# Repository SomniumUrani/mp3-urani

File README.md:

# MP3 - Urani House

## Button layout

## Electric chars

| Description   | Num             | V min | typ | V max | mA  |
| ------------- | --------------- | ----- | --- | ----- | --- |
| MCU           | STM32F412       | 1.7   | -   | 3.6   | 30  |
| MCU           | ESP32           | 3     | 3.3 | 3.6   | 450 |
| LCD backlight | HS24CG003-ARX   | 2.8   | 3   | 3.2   | 80  |
| LCD vdd       | NHS24CG003-ARXA | 1.65  | 1.8 | 3.3   | -   |
| IO expander   | PCF8574T        | 2.5   | -   | 6     | 25  |
| DAC           | PCM5102A        | 3.1   | 3.3 | 3.46  | 10  |

## Components stuff
### Special outsource components on PCB

| Name                  | MPN                   | Source | Source No. | Description                                                                                 |
| --------------------- | --------------------- | ------ | ---------- | ------------------------------------------------------------------------------------------- |
| LCD                   | HS24CG003-ARX         | LCSC   | C5329583   | 240*320 dots (RGB) SPI INTERFACE                                                            |
| FPC connector for LCD | LW10251-16            | LCSC   | C375934    | CONN FFC FPC 16POS 1mm TOP CNT SMD R/A                                                      |
| TF slot               | TF PUSH               | LCSC   | C393941    | CONN MICRO SD CARD (TF CARD) PUSH-PUSH SMD                                                  |
| Debug Slider          | YSSP2AG00             | LCSC   | C5188558   | 300mA Surface Mount,Vertical DPDT 4V SMD Slide Switches RoHS                                |
| Audio Jack            | PJ-393-7A             | LCSC   | C128990    | CONN JACK STEREO 3.5mm SMD                                                                  |
| Crystal oscilator     | 2.D.1.260000704       | LCSC   | C42420962  | CRYSTAL 26MHz 7pF SMD                                                                       |
| PUSH switch           | R4A25211L             | LCSC   | C49393629  | 30,000 cycles 50mA Without SPST-NO Rectangular Button 12V 1.8N SMD Pushbutton Switches RoHS |
| Thermistor            | HNTC0805-104F3950FB   | LCSC   | C49247664  | 100kΩ 140uA 3950K ±1% 200mW ±1% 0805 NTC Thermistors RoHS                                   |
| USB c receptacle      | TYPE-C 16PIN 2MD(073) | LCSC   | C2765186   | CONN RCPT Type-C 16POS SMD R/A                                                              |

### Common components selection

| Name           | MPN                 | Source | Source No. | Description                            |
| -------------- | ------------------- | ------ | ---------- | -------------------------------------- |
| Inductor 1uH   | SNH.4020.TYB1R0MT00 | LCSC   | C2942331   | FIXED IND 1uH 2.15A 0.037Ω SMD,4x4mm   |
| Inductor 2.2uH | MNR4018T220MT       | LCSC   | C18222010  | FIXED IND 22uH 0.36Ω SMD,4x4mm         |
| GREEN LED      | XL-2012UGC          | LCSC   | C965815    | LED EMERALD GREEN WATER CLEAR 0805 SMD |
| BLUE LED       | XL-2012UBC          | LCSC   | C965817    | LED BLUE WATER CLEAR 0805 SMD          |
| RED LED        | XL-2012SURC         | LCSC   | C965812    | LED RED WATER CLEAR 0805 SMD           |

## Communication protocols peripherals

### SPI - MISO/MOSI

| Peripheral | Max speed | Use          |
| ---------- | --------- | ------------ |
| SPI 1      | 50 Mbit/s | LCD          |
| SPI 2      | 25 Mbit/s | None         |
| SPI 3      | 25 Mbit/s | None         |
| SPI 4      | 50 Mbit/s | None         |
| SPI 5      | 50 Mbit/s | LCD touch IC |

### I2C - SDA/SCL

Their frequency can be increased up to 1 MHz. For more details on
the complete solution, refer to the nearest STMicroelectronics sales office.

| Peripheral | Max speed | Use           |
| ---------- | --------- | ------------- |
| I2C x      | 1 MHz     | None          |
| I2C x      | 400 KHz   | HMI expansion |
| I2C x      | 400 KHz   | None          |
| I2C x      | 400 KHz   | None          |

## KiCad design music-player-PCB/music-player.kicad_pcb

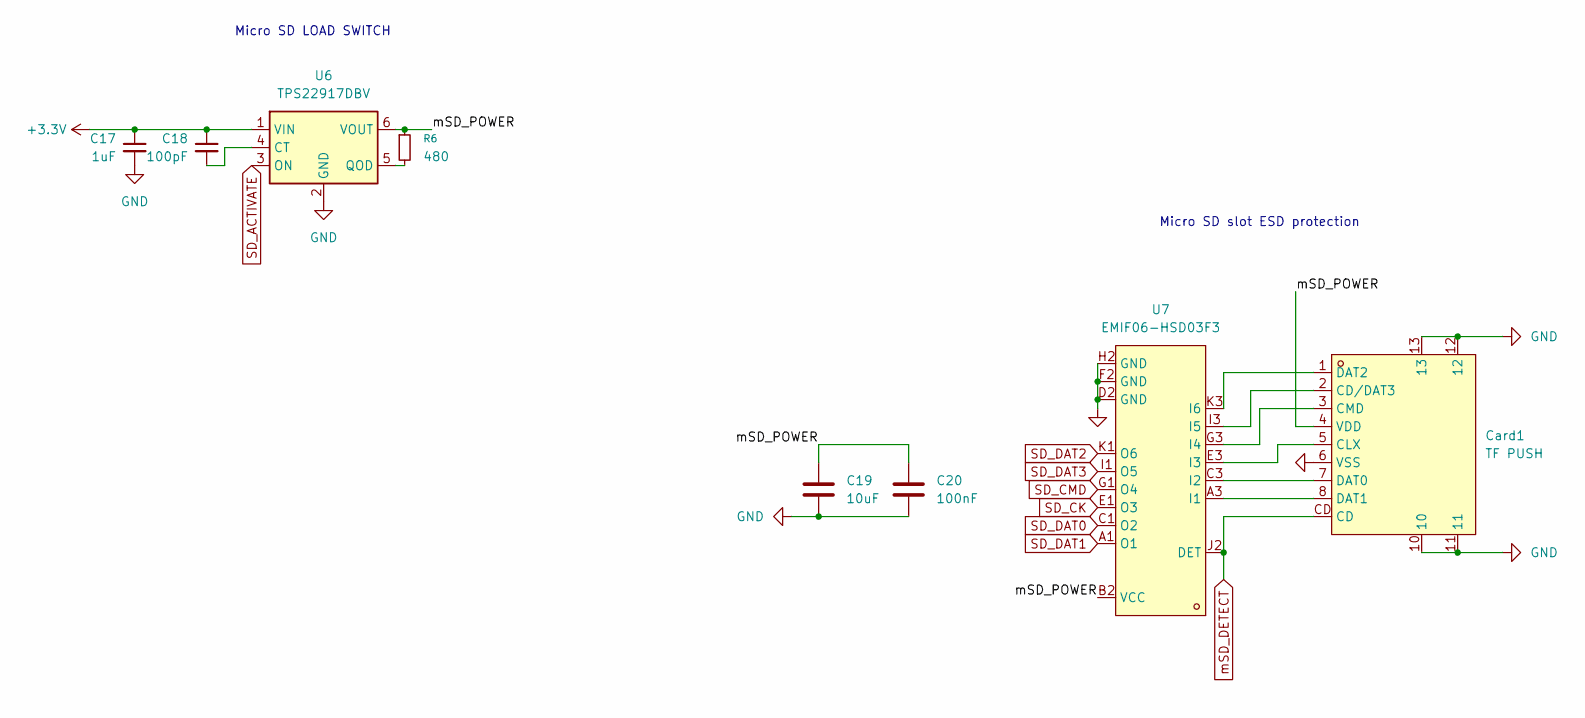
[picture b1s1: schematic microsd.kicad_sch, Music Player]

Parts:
C17: 1uF; C_1206_3216Metric
C18: 100pF; C_0603_1608Metric
C19: 10uF; C_1206_3216Metric
C20: 100nF; C_0603_1608Metric
Card1: TF PUSH; TF-SMD_TF-PUSH; MPN TF PUSH; LCSC Part C393941
R6: 480; R_0805_2012Metric
U6: TPS22917DBV; SOT-23-6
U7: EMIF06-HSD03F3; BGA-17_L2.4-W1.1-P0.20-BL-ST_EMIF06-HSD03F3_1; MPN EMIF06-HSD03F3; LCSC Part C3152872

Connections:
+3.3V: C17.1, C18.1, U6.1 (VIN); also elsewhere on the board
/SD card/mSD_POWER: C19.1, C20.1, Card1.4 (VDD), R6.1, U6.6 (VOUT), U7.B2 (VCC)
GND: C17.2, C19.2, C20.2, Card1.6 (VSS), Card1.10, Card1.11, Card1.12, Card1.13, U6.2 (GND), U7.D2 (GND), U7.F2 (GND), U7.H2 (GND); also elsewhere on the board
unnamed: Card1.2 (CD/DAT3), U7.I3 (I5)
unnamed: Card1.5 (CLX), U7.E3 (I3)
unnamed: Card1.3 (CMD), U7.G3 (I4)
unnamed: Card1.7 (DAT0), U7.C3 (I2)
unnamed: Card1.8 (DAT1), U7.A3 (I1)
unnamed: Card1.1 (DAT2), U7.K3 (I6)
unnamed: C18.2, U6.4 (CT)
unnamed: R6.2, U6.5 (QOD)
SD_ACTIVATE: U6.3 (ON); also elsewhere on the board
SD_CK: U7.E1 (O3); also elsewhere on the board
SD_CMD: U7.G1 (O4); also elsewhere on the board
SD_DAT0: U7.C1 (O2); also elsewhere on the board
SD_DAT1: U7.A1 (O1); also elsewhere on the board
SD_DAT2: U7.K1 (O6); also elsewhere on the board
SD_DAT3: U7.I1 (O5); also elsewhere on the board
mSD_DETECT: Card1.CD, U7.J2 (DET); also elsewhere on the board

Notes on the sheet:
Micro SD slot ESD protection
Micro SD LOAD SWITCH

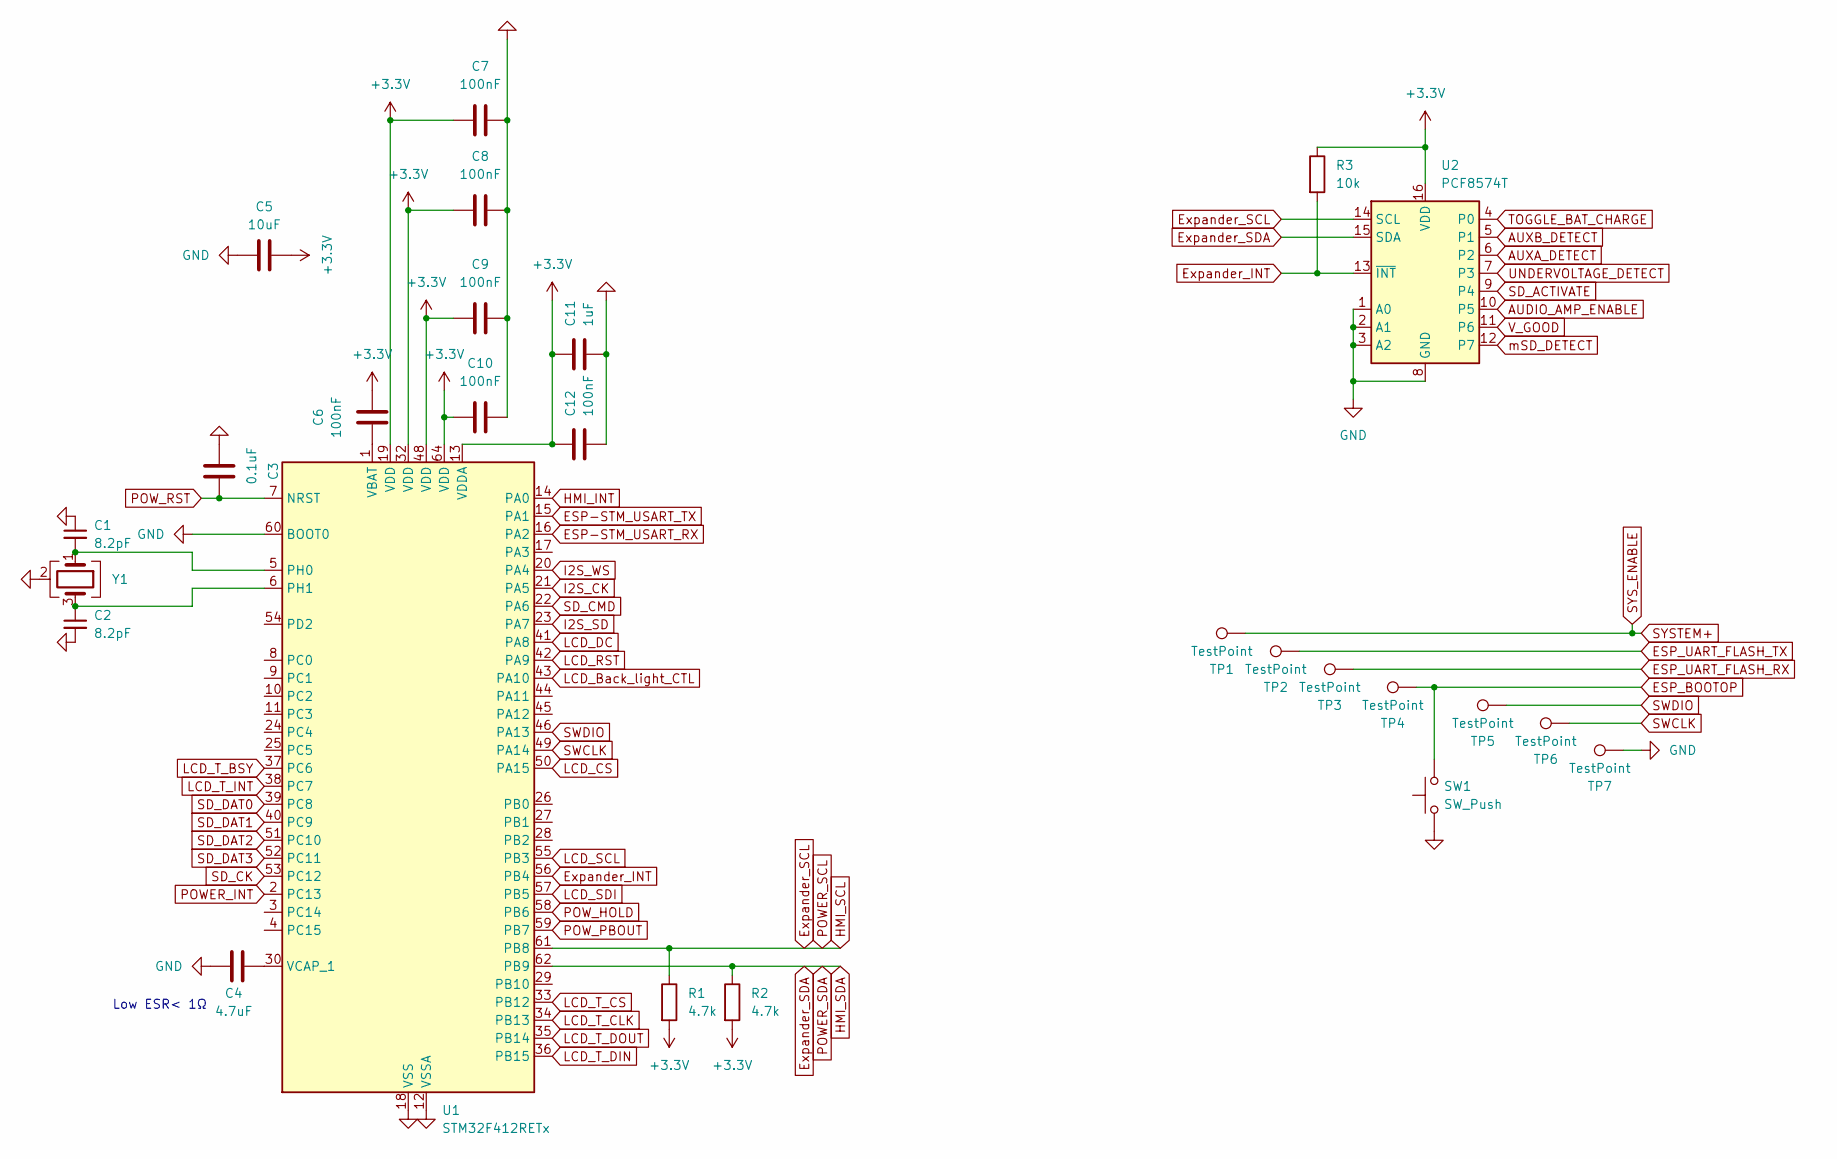
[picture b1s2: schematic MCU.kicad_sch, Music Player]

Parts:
C1, C2: 8.2pF; C_0603_1608Metric
C3: 0.1uF; C_0603_1608Metric
C4: 4.7uF; C_0402_1005Metric
C5: 10uF; C_0603_1608Metric
C6, C7, C8, C9, C10, C12: 100nF; C_0402_1005Metric
C11: 1uF; C_0402_1005Metric
R1, R2: 4.7k; R_01005_0402Metric
R3: 10k; R_01005_0402Metric
SW1: SW_Push; SW-SMD_L6.0-W3.5-LS8.0-1
TP1, TP2, TP3, TP4, TP5, TP6, TP7: TestPoint; TestPoint_Pad_1.5x1.5mm
U1: STM32F412RETx; LQFP-64_10x10mm_P0.5mm
U2: PCF8574T; SOIC-16W_7.5x10.3mm_P1.27mm
Y1: 2.D.1.260000704; Crystal_SMD_2016-4Pin_2.0x1.6mm

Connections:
+3.3V: C5.2, C6.1, C7.2, C8.2, C9.2, C10.2, C11.1, C12.2, R1.2, R2.2, R3.1, U1.13 (VDDA), U1.19 (VDD), U1.32 (VDD), U1.48 (VDD), U1.64 (VDD), U2.16 (VDD); also elsewhere on the board
AUDIO_AMP_ENABLE: U2.10 (P5); also elsewhere on the board
AUXA_DETECT: U2.6 (P2); also elsewhere on the board
AUXB_DETECT: U2.5 (P1); also elsewhere on the board
ESP-STM_USART_RX: U1.16 (PA2); also elsewhere on the board
ESP-STM_USART_TX: U1.15 (PA1); also elsewhere on the board
ESP_BOOTOP: SW1.2, TP4.1 (1_1); also elsewhere on the board
ESP_UART_FLASH_RX: TP3.1 (1_1); also elsewhere on the board
ESP_UART_FLASH_TX: TP2.1 (1_1); also elsewhere on the board
Expander_INT: R3.2, U1.56 (PB4), U2.13 (~INT)
Expander_SCL: R1.1, U1.61 (PB8), U2.14 (SCL); also elsewhere on the board
Expander_SDA: R2.1, U1.62 (PB9), U2.15 (SDA); also elsewhere on the board
GND: C1.1, C2.2, C3.1, C4.1, C5.1, C7.1, C8.1, C9.1, C10.1, C11.2, C12.1, SW1.1, TP7.1 (1_1), U1.12 (VSSA), U1.18 (VSS), U1.31 (VSS), U1.47 (VSS), U1.60 (BOOT0), U1.63 (VSS), U2.1 (A0), U2.2 (A1), U2.3 (A2), U2.8 (GND), Y1.2 (G), Y1.4 (G); also elsewhere on the board
HMI_INT: U1.14 (PA0); also elsewhere on the board
I2S_CK: U1.21 (PA5); also elsewhere on the board
I2S_SD: U1.23 (PA7); also elsewhere on the board
I2S_WS: U1.20 (PA4); also elsewhere on the board
LCD_Back_light_CTL: U1.43 (PA10); also elsewhere on the board
LCD_CS: U1.50 (PA15); also elsewhere on the board
LCD_DC: U1.41 (PA8); also elsewhere on the board
LCD_RST: U1.42 (PA9); also elsewhere on the board
LCD_SCL: U1.55 (PB3); also elsewhere on the board
LCD_SDI: U1.57 (PB5); also elsewhere on the board
LCD_T_BSY: U1.37 (PC6); also elsewhere on the board
LCD_T_CLK: U1.34 (PB13); also elsewhere on the board
LCD_T_CS: U1.33 (PB12); also elsewhere on the board
LCD_T_DIN: U1.36 (PB15); also elsewhere on the board
LCD_T_DOUT: U1.35 (PB14); also elsewhere on the board
LCD_T_INT: U1.38 (PC7); also elsewhere on the board
unnamed: C1.2, U1.5 (PH0), Y1.1
unnamed: C2.1, U1.6 (PH1), Y1.3
unnamed: C6.2, U1.1 (VBAT)
unnamed: C4.2, U1.30 (VCAP_1)
POWER_INT: U1.2 (PC13); also elsewhere on the board
POW_HOLD: U1.58 (PB6); also elsewhere on the board
POW_PBOUT: U1.59 (PB7); also elsewhere on the board
POW_RST: C3.2, U1.7 (NRST); also elsewhere on the board
SD_ACTIVATE: U2.9 (P4); also elsewhere on the board
SD_CK: U1.53 (PC12); also elsewhere on the board
SD_CMD: U1.22 (PA6); also elsewhere on the board
SD_DAT0: U1.39 (PC8); also elsewhere on the board
SD_DAT1: U1.40 (PC9); also elsewhere on the board
SD_DAT2: U1.51 (PC10); also elsewhere on the board
SD_DAT3: U1.52 (PC11); also elsewhere on the board
SWCLK: TP6.1 (1_1), U1.49 (PA14)
SWDIO: TP5.1 (1_1), U1.46 (PA13)
SYSTEM+: TP1.1 (1_1); also elsewhere on the board
TOGGLE_BAT_CHARGE: U2.4 (P0); also elsewhere on the board
UNDERVOLTAGE_DETECT: U2.7 (P3); also elsewhere on the board
V_GOOD: U2.11 (P6); also elsewhere on the board
mSD_DETECT: U2.12 (P7); also elsewhere on the board

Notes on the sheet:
Low ESR< 1Ω

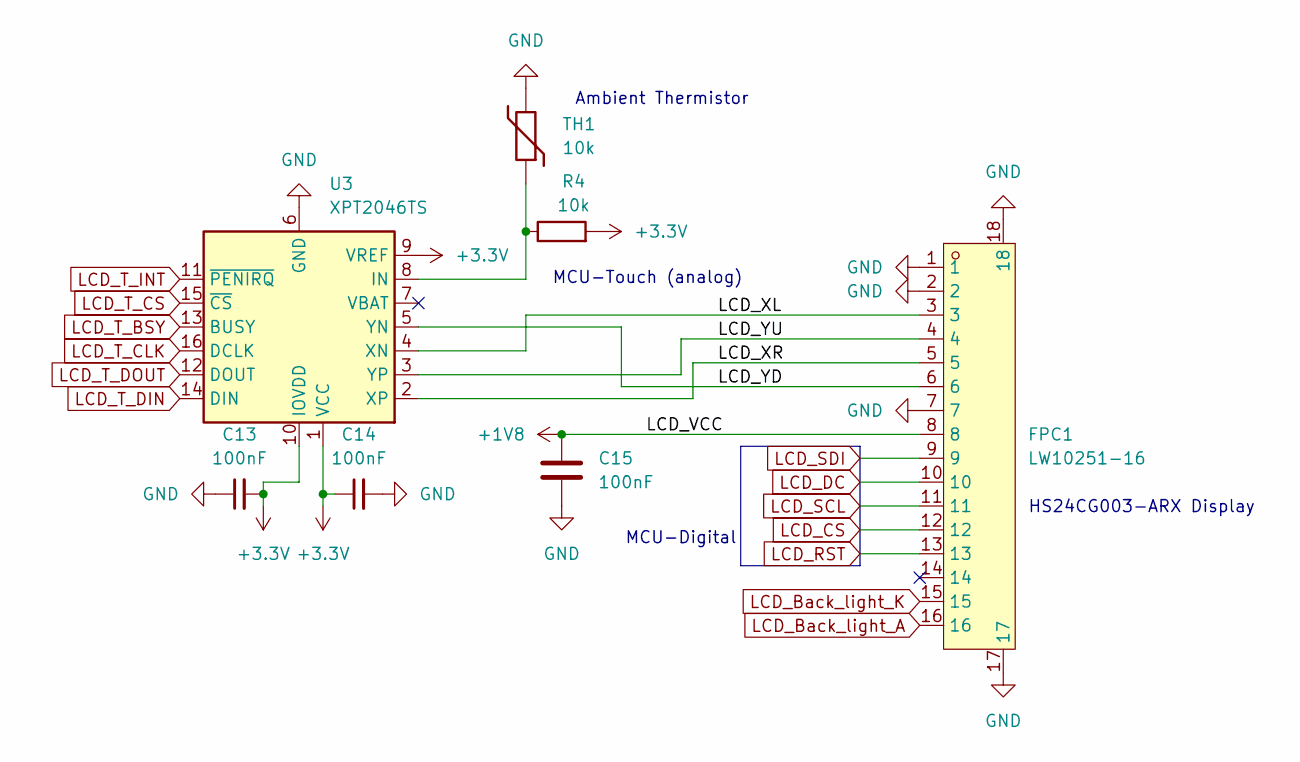
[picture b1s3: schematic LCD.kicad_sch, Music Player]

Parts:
C13, C14, C15: 100nF; C_0603_1608Metric
FPC1: LW10251-16; FFC-SMD_16P-P01.00_LW10251-16; MPN LW10251-16; LCSC Part C375934
R4: 10k; R_01005_0402Metric
TH1: 10k; R0805
U3: XPT2046TS; TSSOP-16_4.4x5mm_P0.65mm

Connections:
+1V8: C15.1, FPC1.8; also elsewhere on the board
+3.3V: C13.2, C14.1, R4.2, U3.1 (VCC), U3.9 (VREF), U3.10 (IOVDD); also elsewhere on the board
/LCD/LCD_XL: FPC1.3, U3.4 (XN)
/LCD/LCD_XR: FPC1.5, U3.2 (XP)
/LCD/LCD_YD: FPC1.6, U3.5 (YN)
/LCD/LCD_YU: FPC1.4, U3.3 (YP)
GND: C13.1, C14.2, C15.2, FPC1.1, FPC1.2, FPC1.7, FPC1.17, FPC1.18, TH1.2, U3.6 (GND); also elsewhere on the board
LCD_Back_light_A: FPC1.16; also elsewhere on the board
LCD_Back_light_K: FPC1.15; also elsewhere on the board
LCD_CS: FPC1.12; also elsewhere on the board
LCD_DC: FPC1.10; also elsewhere on the board
LCD_RST: FPC1.13; also elsewhere on the board
LCD_SCL: FPC1.11; also elsewhere on the board
LCD_SDI: FPC1.9; also elsewhere on the board
LCD_T_BSY: U3.13 (BUSY); also elsewhere on the board
LCD_T_CLK: U3.16 (DCLK); also elsewhere on the board
LCD_T_CS: U3.15 (~CS); also elsewhere on the board
LCD_T_DIN: U3.14 (DIN); also elsewhere on the board
LCD_T_DOUT: U3.12 (DOUT); also elsewhere on the board
LCD_T_INT: U3.11 (~PENIRQ); also elsewhere on the board
unnamed: R4.1, TH1.1, U3.8 (IN)

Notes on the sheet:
Ambient Thermistor
HS24CG003-ARX Display
MCU-Digital
MCU-Touch (analog)

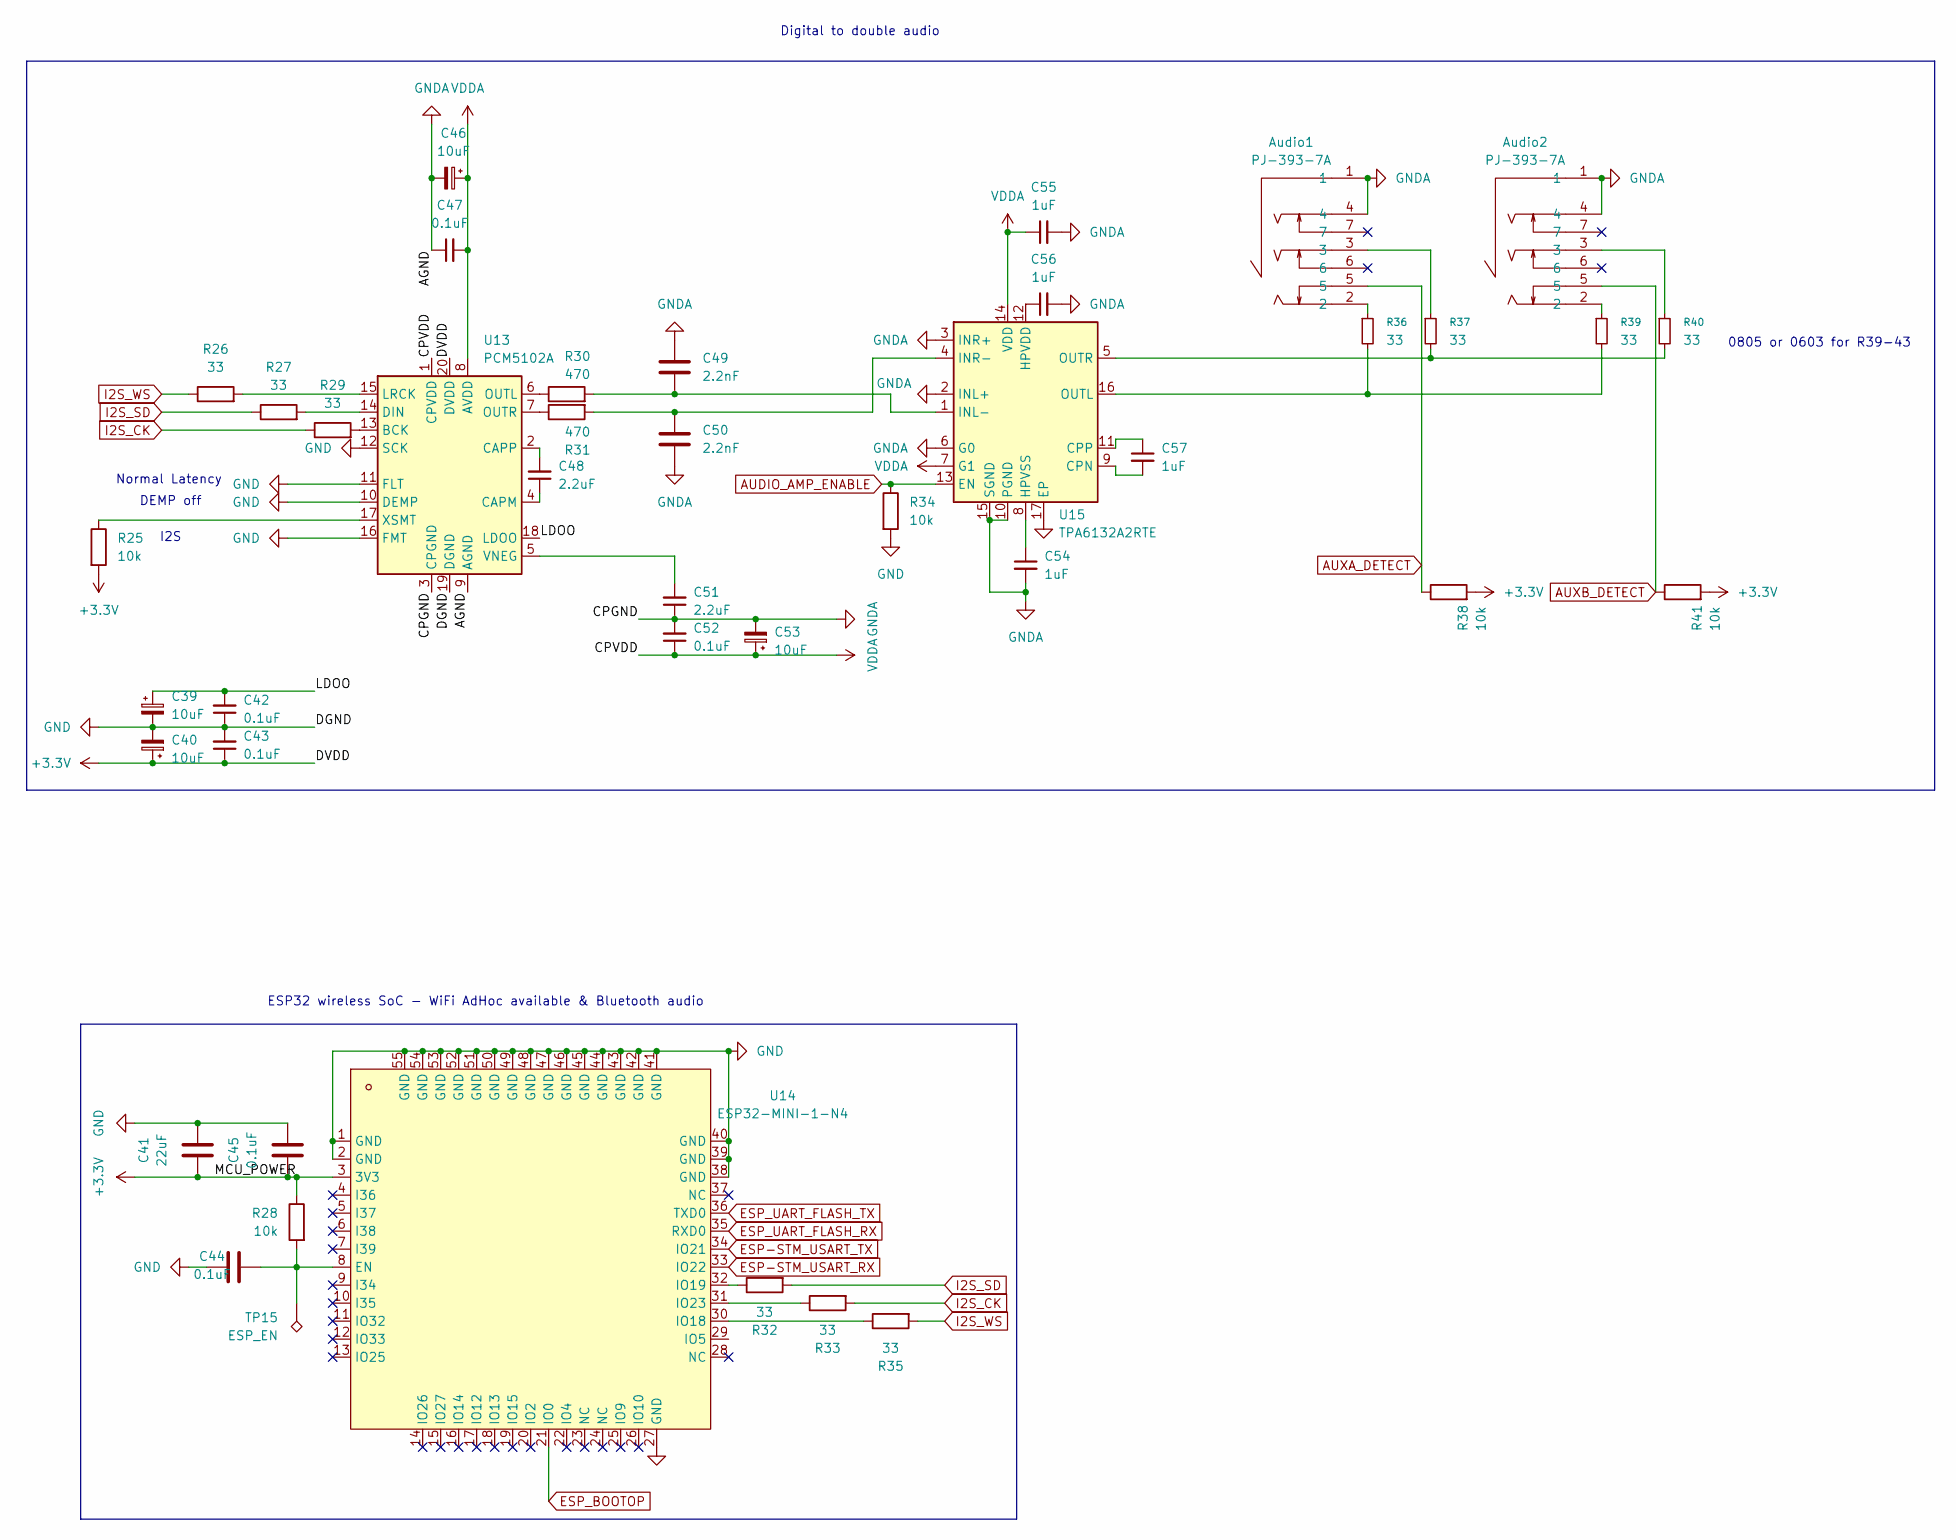
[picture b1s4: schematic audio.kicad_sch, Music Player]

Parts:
Audio1, Audio2: PJ-393-7A; AUDIO-SMD_PJ-393-7A; MPN PJ-393-7A; LCSC Part C128990
C39, C40, C46, C53: 10uF; C_1206_3216Metric
C41: 22uF; C_1206_3216Metric
C42, C43, C44, C45, C47, C52: 0.1uF; C_0603_1608Metric
C48, C51: 2.2uF; C_1206_3216Metric
C49, C50: 2.2nF; C_1206_3216Metric
C54, C55, C56, C57: 1uF; C_1206_3216Metric
R25, R28, R34, R38, R41: 10k; R_01005_0402Metric
R26, R27, R29, R32, R33, R35, R36, R37, R39, R40: 33; R_01005_0402Metric
R30, R31: 470; R_01005_0402Metric
TP15: ESP_EN; TestPoint_Pad_1.5x1.5mm
U13: PCM5102A; TSSOP-20_4.4x6.5mm_P0.65mm
U14: ESP32-MINI-1-N4; WIFI-SMD_ESP32-MINI-1; MPN ESP32-MINI-1-N4; LCSC Part C2980305
U15: TPA6132A2RTE; WQFN-16-1EP_3x3mm_P0.5mm_EP1.6x1.6mm_ThermalVias

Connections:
+3.3V: C40.1, C41.1, C43.1, C45.1, R25.2, R28.1, R38.2, R41.2, U13.20 (DVDD), U14.3 (3V3); also elsewhere on the board
/Audio/LDOO: C39.1, C42.2, U13.18 (LDOO)
AUDIO_AMP_ENABLE: R34.1, U15.13 (EN); also elsewhere on the board
AUXA_DETECT: Audio1.5, R38.1; also elsewhere on the board
AUXB_DETECT: Audio2.5, R41.1; also elsewhere on the board
ESP-STM_USART_RX: U14.33 (IO22); also elsewhere on the board
ESP-STM_USART_TX: U14.34 (IO21); also elsewhere on the board
ESP_BOOTOP: U14.21 (IO0); also elsewhere on the board
ESP_UART_FLASH_RX: U14.35 (RXD0); also elsewhere on the board
ESP_UART_FLASH_TX: U14.36 (TXD0); also elsewhere on the board
GND: Audio1.1, Audio1.4, Audio2.1, Audio2.4, C39.2, C40.2, C41.2, C42.1, C43.2, C44.1, C45.2, C46.2, C47.1, C49.1, C50.2, C51.1, C52.2, C53.2, C54.2, C55.2, C56.2, R34.2, U13.3 (CPGND), U13.9 (AGND), U13.10 (DEMP), U13.11 (FLT), U13.12 (SCK), U13.16 (FMT), U13.19 (DGND), U14.1 (GND), U14.2 (GND), U14.27 (GND), U14.38 (GND), U14.39 (GND), U14.40 (GND), U14.41 (GND), U14.42 (GND), U14.43 (GND), U14.44 (GND), U14.45 (GND), U14.46 (GND), U14.47 (GND), U14.48 (GND), U14.49 (GND), U14.50 (GND), U14.51 (GND), U14.52 (GND), U14.53 (GND), U14.54 (GND), U14.55 (GND), U15.2 (INL+), U15.3 (INR+), U15.6 (G0), U15.10 (PGND), U15.15 (SGND), U15.17 (EP); also elsewhere on the board
I2S_CK: R29.1, R33.2; also elsewhere on the board
I2S_SD: R27.1, R32.2; also elsewhere on the board
I2S_WS: R26.1, R35.2; also elsewhere on the board
unnamed: Audio1.2, R36.1
unnamed: Audio1.3, R37.1
unnamed: Audio2.2, R39.1
unnamed: Audio2.3, R40.1
unnamed: R29.2, U13.13 (BCK)
unnamed: C48.1, U13.4 (CAPM)
unnamed: C48.2, U13.2 (CAPP)
unnamed: R27.2, U13.14 (DIN)
unnamed: R26.2, U13.15 (LRCK)
unnamed: R30.1, U13.6 (OUTL)
unnamed: R31.1, U13.7 (OUTR)
unnamed: C51.2, U13.5 (VNEG)
unnamed: R25.1, U13.17 (XSMT)
unnamed: C44.2, R28.2, TP15.1 (1_1), U14.8 (EN)
unnamed: R35.1, U14.30 (IO18)
unnamed: R32.1, U14.32 (IO19)
unnamed: R33.1, U14.31 (IO23)
unnamed: C57.2, U15.9 (CPN)
unnamed: C57.1, U15.11 (CPP)
unnamed: C56.1, U15.12 (HPVDD)
unnamed: C54.1, U15.8 (HPVSS)
unnamed: C49.2, R30.2, U15.1 (INL-)
unnamed: C50.1, R31.2, U15.4 (INR-)
unnamed: R36.2, R39.2, U15.16 (OUTL)
unnamed: R37.2, R40.2, U15.5 (OUTR)
VDDA: C46.1, C47.2, C52.1, C53.1, C55.1, U13.1 (CPVDD), U13.8 (AVDD), U15.7 (G1), U15.14 (VDD); also elsewhere on the board

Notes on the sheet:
DEMP off
Normal Latency
ESP32 wireless SoC - WiFi AdHoc available & Bluetooth audio
Digital to double audio
I2S
0805 or 0603 for R39-43

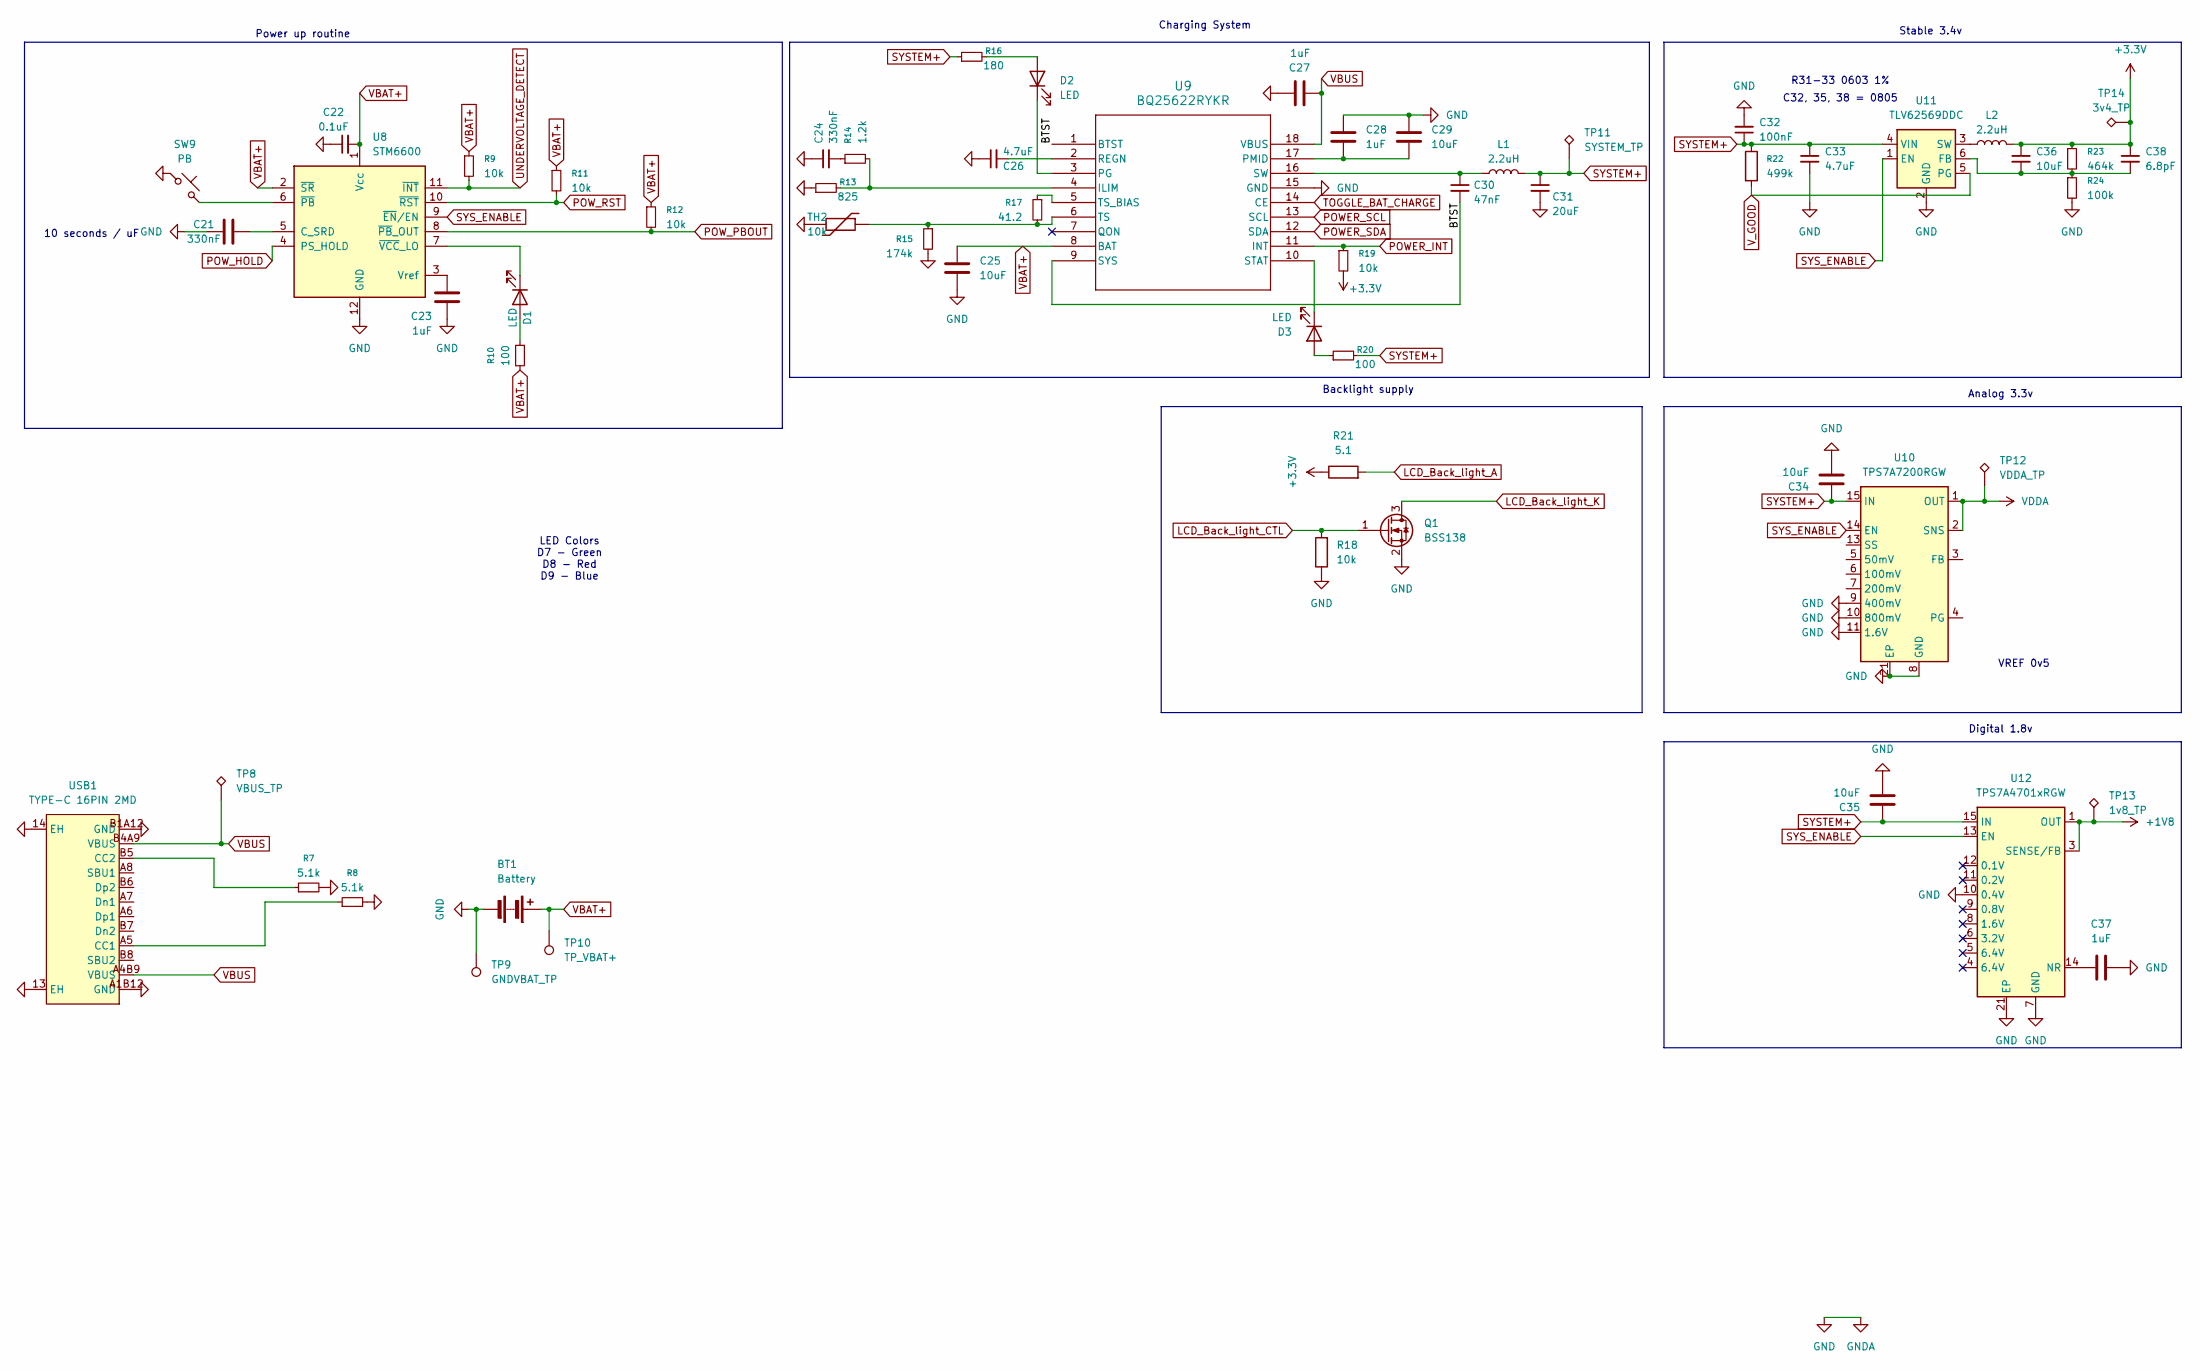
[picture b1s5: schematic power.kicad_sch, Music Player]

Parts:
BT1: Battery; JST_PH_S2B-PH-SM4-TB_1x02-1MP_P2.00mm_Horizontal
C21, C24: 330nF; C_0603_1608Metric
C22: 0.1uF; C_0603_1608Metric
C23, C27, C28, C37: 1uF; C_1206_3216Metric
C25, C29, C34, C35: 10uF; C_1206_3216Metric
C26: 4.7uF; C_1206_3216Metric
C30: 47nF; C_1206_3216Metric
C31: 20uF; C_1206_3216Metric
C32: 100nF; C_0603_1608Metric
C33: 4.7uF; R_0805_2012Metric
C36: 10uF; R_0805_2012Metric
C38: 6.8pF; R_0805_2012Metric
D1, D2, D3: LED; LED_0805_2012Metric
L1, L2: 2.2uH; L_Taiyo-Yuden_NR-40xx
Q1: BSS138; SOT-23
R7, R8: 5.1k; R_01005_0402Metric
R9, R11, R12: 10k; R_01005_0402Metric
R10, R20: 100; R_01005_0402Metric
R13: 825; R_0805_2012Metric
R14: 1.2k; R_01005_0402Metric
R15: 174k; R_01005_0402Metric
R16: 180; R_01005_0402Metric
R17: 41.2; R_01005_0402Metric
R18, R19: 10k; R_0805_2012Metric
R21: 5.1; R_0805_2012Metric
R22: 499k; R_0603_1608Metric
R23: 464k; R_0603_1608Metric
R24: 100k; R_0603_1608Metric
SW9: PB; SW-SMD_L6.0-W3.5-LS8.0-1
TH2: 10k; R0805
TP8: VBUS_TP; TestPoint_Pad_1.5x1.5mm
TP9: GNDVBAT_TP; TestPoint_Pad_1.5x1.5mm
TP10: TP_VBAT+; TestPoint_Pad_1.5x1.5mm
TP11: SYSTEM_TP; TestPoint_Pad_1.5x1.5mm
TP12: VDDA_TP; TestPoint_Pad_1.5x1.5mm
TP13: 1v8_TP; TestPoint_Pad_1.5x1.5mm
TP14: 3v4_TP; TestPoint_Pad_1.5x1.5mm
U8: STM6600; TDFN-12_2x3mm_P0.5mm
U9: BQ25622RYKR; WQFN-HR18__RYK_TEX
U10: TPS7A7200RGW; Texas_RGW0020A_VQFN-20-1EP_5x5mm_P0.65mm_EP3.15x3.15mm_Ther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
U11: TLV62569DDC; SOT-23-6
U12: TPS7A4701xRGW; Texas_RGW0020A_VQFN-20-1EP_5x5mm_P0.65mm_EP3.15x3.15mm_Ther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
USB1: TYPE-C 16PIN 2MD; USB-C-SMD_TYPE-C-16PIN-2MD-073; MPN TYPE-C 16PIN 2MD(073); LCSC Part C2765186

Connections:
+1V8: TP13.1 (1_1), U12.1 (OUT), U12.3 (SENSE/FB), U12.20 (OUT); also elsewhere on the board
+3.3V: C36.1, C38.1, L2.2, R19.2, R21.1, R23.1, TP14.1 (1_1); also elsewhere on the board
/Power/BTST: C30.2, U9.1 (BTST), U9.9 (SYS)
Expander_SCL: U9.13 (SCL); also elsewhere on the board
Expander_SDA: U9.12 (SDA); also elsewhere on the board
GND: BT1.2 (-), BT1.MP, C21.2, C22.1, C23.1, C24.1, C25.2, C26.1, C27.1, C28.1, C29.1, C31.2, C32.2, C33.2, C34.1, C35.1, C37.2, Q1.2 (S), R7.2, R8.2, R13.1, R15.2, R18.1, R24.2, SW9.1, TH2.2, TP9.1 (1_1), U8.12 (GND), U9.15 (GND), U10.8 (GND), U10.9 (400mV), U10.10 (800mV), U10.11 (1.6V), U10.18 (GND), U10.21 (EP), U11.2 (GND), U12.7 (GND), U12.10 (0.4V), U12.21 (EP), USB1.13 (EH), USB1.14 (EH), USB1.A1B12 (GND), USB1.B1A12 (GND); also elsewhere on the board
LCD_Back_light_A: R21.2; also elsewhere on the board
LCD_Back_light_CTL: Q1.1 (G), R18.2; also elsewhere on the board
LCD_Back_light_K: Q1.3 (D); also elsewhere on the board
unnamed: C24.2, R14.1
unnamed: D1.2 (A), R10.1
unnamed: D1.1 (K), U8.7 (~VCC_LO)
unnamed: D2.2 (A), R16.2
unnamed: D2.1 (K), U9.3 (PG)
unnamed: D3.2 (A), R20.1
unnamed: D3.1 (K), U9.10 (STAT)
unnamed: C21.1, U8.5 (C_SRD)
unnamed: C23.2, U8.3 (Vref)
unnamed: SW9.2, U8.6 (~PB)
unnamed: R13.2, R14.2, U9.4 (ILIM)
unnamed: C28.2, C29.2, U9.17 (PMID)
unnamed: C26.2, U9.2 (REGN)
unnamed: C30.1, L1.1, U9.16 (SW)
unnamed: R15.1, R17.2, TH2.1, U9.6 (TS)
unnamed: R17.1, U9.5 (TS_BIAS)
unnamed: C36.2, C38.2, R23.2, R24.1, U11.6 (FB)
unnamed: L2.1, U11.3 (SW)
unnamed: C37.1, U12.14 (NR)
unnamed: R8.1, USB1.A5 (CC1)
unnamed: R7.1, USB1.B5 (CC2)
POWER_INT: R19.1, U9.11 (INT); also elsewhere on the board
POW_HOLD: U8.4 (PS_HOLD); also elsewhere on the board
POW_PBOUT: R12.2, U8.8 (~PB_OUT); also elsewhere on the board
POW_RST: R11.2, U8.10 (~RST); also elsewhere on the board
SYSTEM+: C31.1, C32.1, C33.1, C34.2, C35.2, L1.2, R16.1, R20.2, R22.1, TP11.1 (1_1), U8.9 (~EN/EN), U10.14 (EN), U10.15 (IN), U10.16 (IN), U10.17 (IN), U11.1 (EN), U11.4 (VIN), U12.13 (EN), U12.15 (IN), U12.16 (IN); also elsewhere on the board
TOGGLE_BAT_CHARGE: U9.14 (CE); also elsewhere on the board
UNDERVOLTAGE_DETECT: R9.2, U8.11 (~INT); also elsewhere on the board
VBAT+: BT1.1 (+), C22.2, C25.1, R9.1, R10.2, R11.1, R12.1, TP10.1 (1_1), U8.1 (Vcc), U8.2 (~SR), U9.8 (BAT)
VBUS: C27.2, TP8.1 (1_1), U9.18 (VBUS), USB1.A4B9 (VBUS), USB1.B4A9 (VBUS)
VDDA: TP12.1 (1_1), U10.1 (OUT), U10.2 (SNS), U10.19 (OUT), U10.20 (OUT); also elsewhere on the board
V_GOOD: R22.2, U11.5 (PG); also elsewhere on the board

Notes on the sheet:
Backlight supply
Analog 3.3v
LED Colors D7 - Green D8 - Red D9 - Blue
Charging System
VREF 0v5
Stable 3.4v
10 seconds / uF
Digital 1.8v
Power up routine
R31-33 0603 1%
C32, 35, 38 = 0805

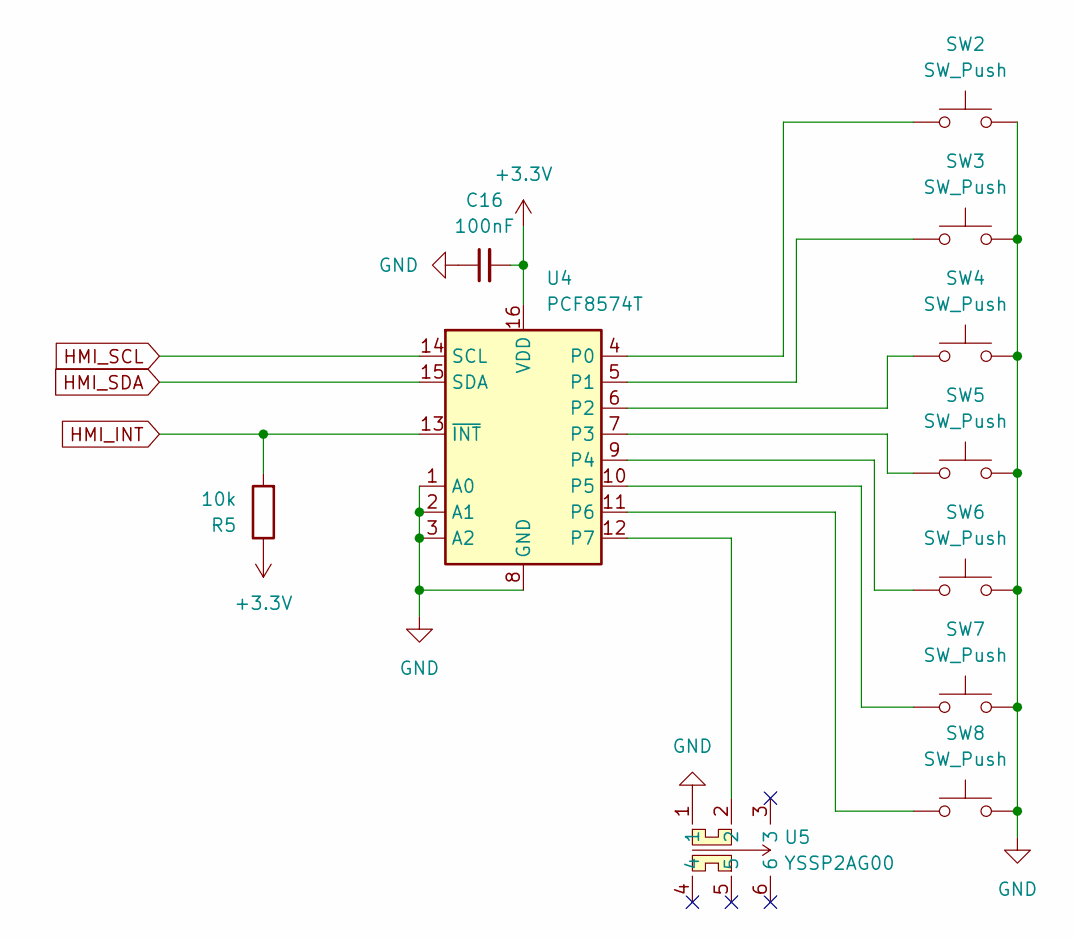
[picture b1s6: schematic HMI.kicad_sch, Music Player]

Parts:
C16: 100nF; C_0603_1608Metric
R5: 10k; R_01005_0402Metric
SW2, SW3, SW4, SW5, SW6, SW7, SW8: SW_Push; SW-SMD_L6.0-W3.5-LS8.0-1
U4: PCF8574T; SOIC-16W_7.5x10.3mm_P1.27mm
U5: YSSP2AG00; SW-SMD_YSSP2AG00; MPN YSSP2AG00; LCSC Part C5188558

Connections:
+3.3V: C16.2, R5.1, U4.16 (VDD); also elsewhere on the board
Expander_SCL: U4.14 (SCL); also elsewhere on the board
Expander_SDA: U4.15 (SDA); also elsewhere on the board
GND: C16.1, SW2.2, SW3.2, SW4.2, SW5.2, SW6.2, SW7.2, SW8.2, U4.1 (A0), U4.2 (A1), U4.3 (A2), U4.8 (GND), U5.1; also elsewhere on the board
HMI_INT: R5.2, U4.13 (~INT); also elsewhere on the board
unnamed: SW2.1, U4.4 (P0)
unnamed: SW3.1, U4.5 (P1)
unnamed: SW4.1, U4.6 (P2)
unnamed: SW5.1, U4.7 (P3)
unnamed: SW6.1, U4.9 (P4)
unnamed: SW7.1, U4.10 (P5)
unnamed: SW8.1, U4.11 (P6)
unnamed: U4.12 (P7), U5.2
